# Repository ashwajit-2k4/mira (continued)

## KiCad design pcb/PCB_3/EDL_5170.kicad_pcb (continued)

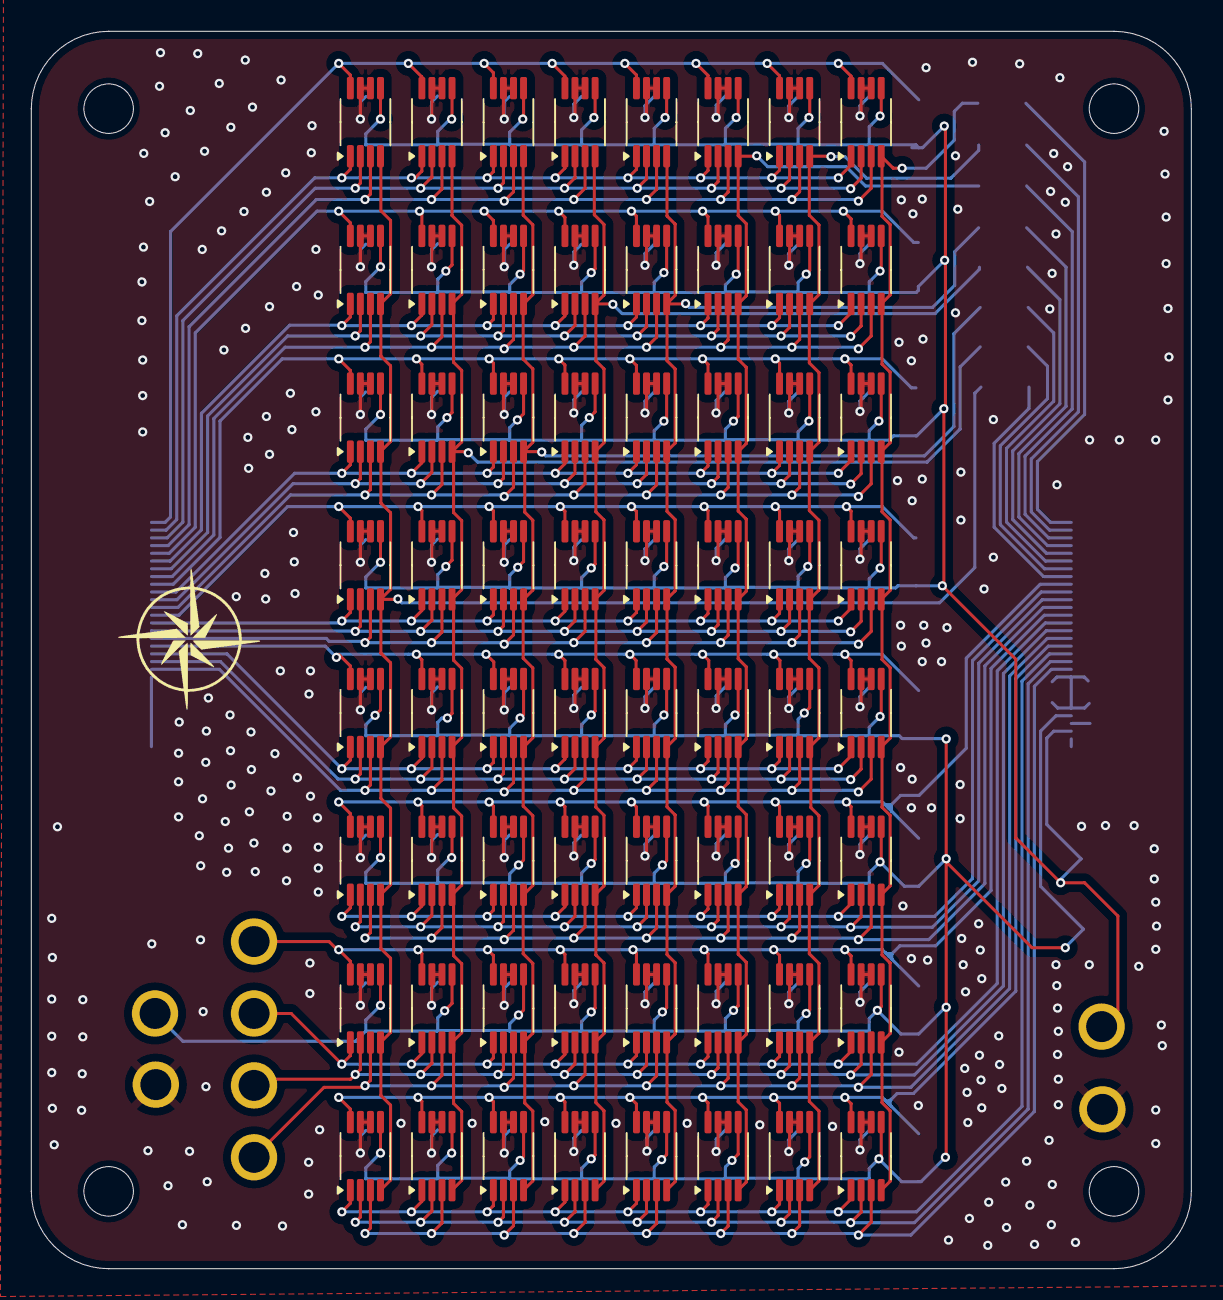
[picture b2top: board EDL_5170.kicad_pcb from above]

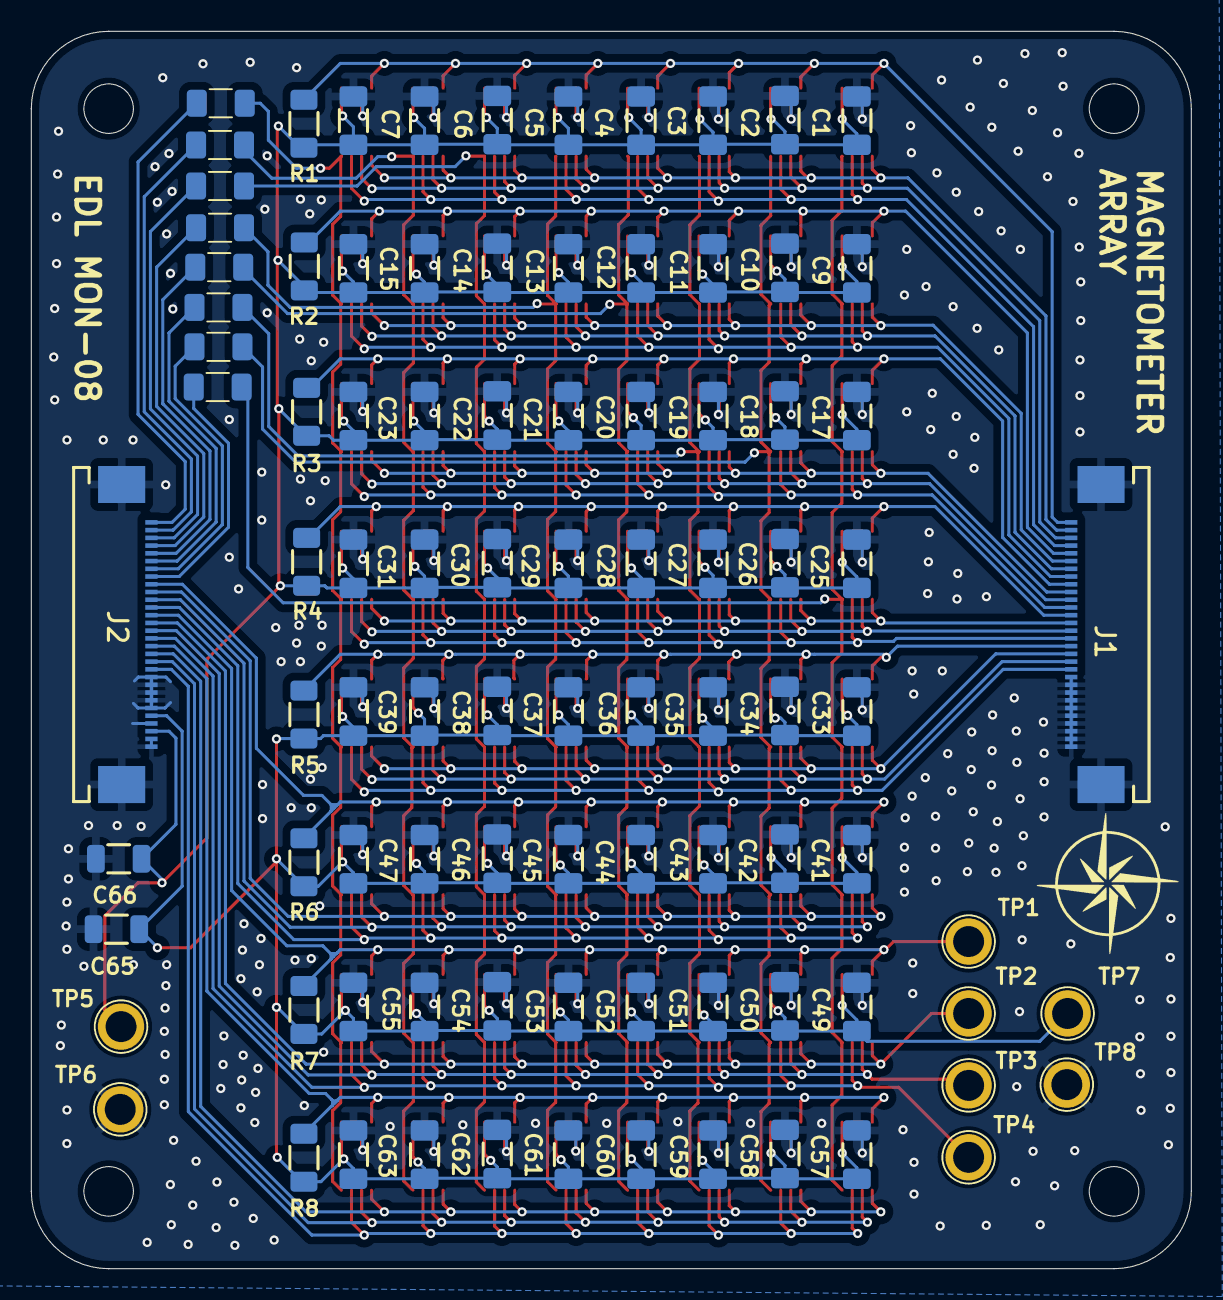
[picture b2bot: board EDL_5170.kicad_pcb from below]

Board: 2 copper layers, 75.0 x 80.0 mm, 156 parts (92 on the bottom side), 51 nets.

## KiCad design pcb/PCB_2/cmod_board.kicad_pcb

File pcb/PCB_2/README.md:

# CMOD Interface PCB

This PCB is designed to work in conjunction with the **TMAG3001 Sensor Array PCB**, forming a complete sensor head system. It serves as the interface between the microcontroller and the sensor array.

## Overview

- **Purpose**: Interface the TMAG3001 sensor array with a CMOD FPGA module  
- **CMOD Support**: Two sets of pin headers to securely mount the CMOD  
- **Signal Routing**: All signals are routed via ribbon cable connectors coming from the TMAG3001 Sensor Array PCB  
- **Power Supply**:  
  - Screw terminal block for providing power to both the FPGA and the sensor array  
  - Switches included to control the power supply to different sections

---

## Features

- **Ribbon Cable Connectors**:  
  - Located on both edges of the PCB  
  - Carry all signal lines from the sensor array PCB  

- **Power Interface**:  
  - Screw terminal for 3.3V/5V input  
  - Power control switches to selectively enable/disable supply to the FPGA and sensor PCB  

- **Mechanical Support**:  
  - Dual header slots to mount a CMOD A7 or similar FPGA board securely

---

## Files & Resources

The repository folders include:
- **Schematic**
- **PCB Layout**
- **3D Renders**
- **Assembled PCB Images**

---

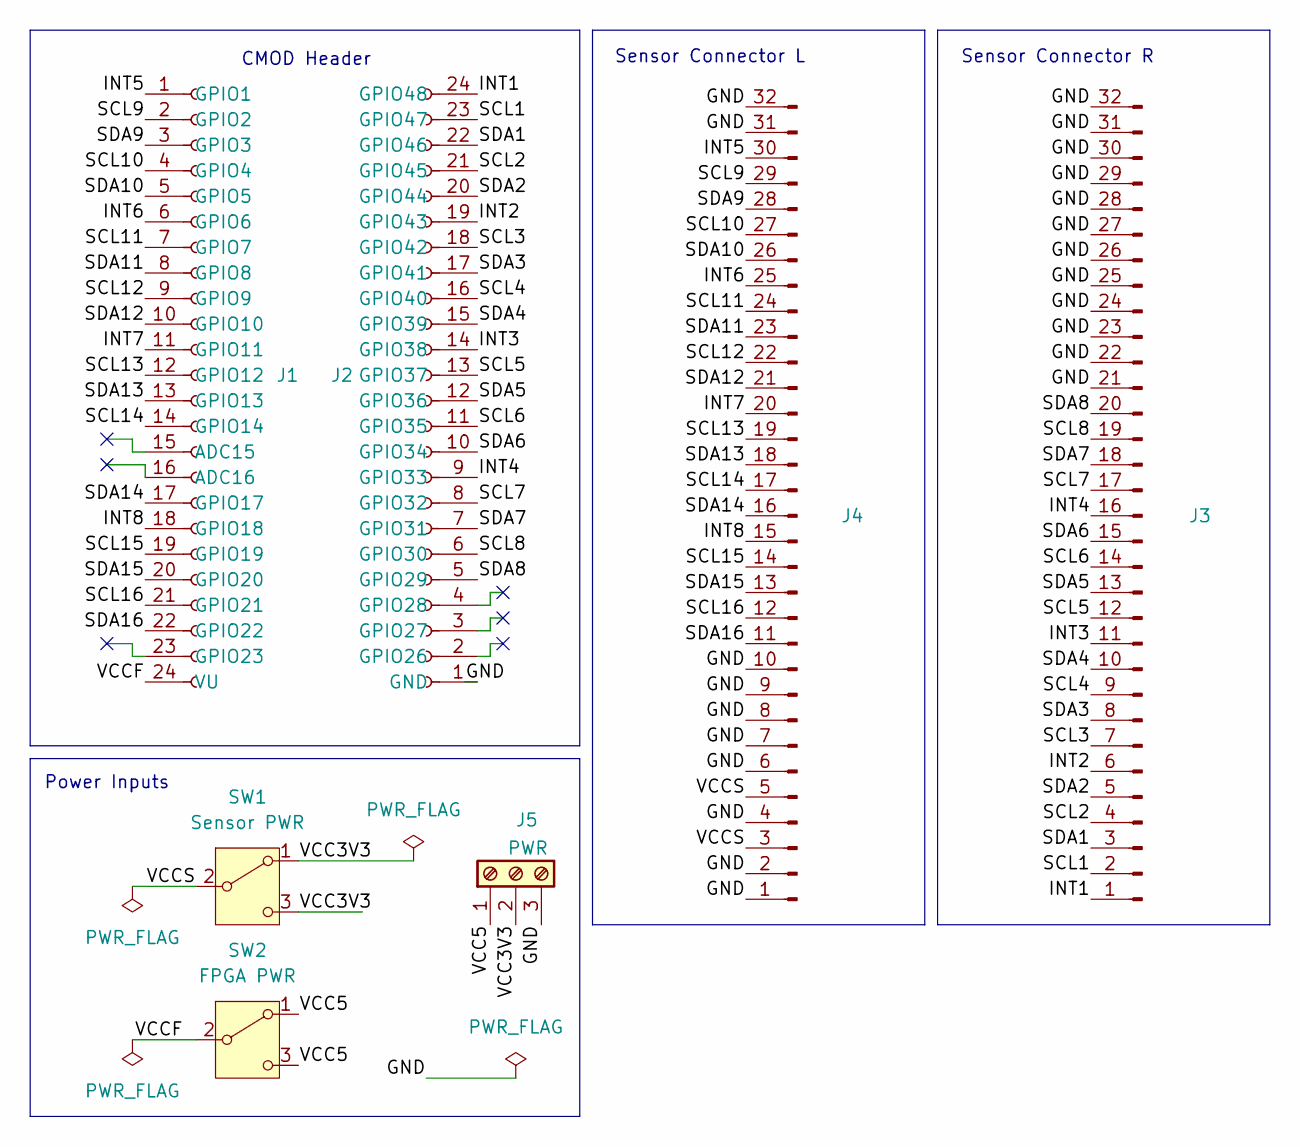
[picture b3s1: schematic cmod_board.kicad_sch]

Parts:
J1: PinSocket_1x24_P2.54mm_Vertical
J2: Conn_01x24_Socket; PinSocket_1x24_P2.54mm_Vertical
J3, J4: Conn_01x32_Pin; 52435-3071
J5: PWR; TerminalBlock_Phoenix_PT-1,5-3-3.5-H_1x03_P3.50mm_Horizontal
SW1: Sensor PWR; SPDT Switch 3 mm
SW2: FPGA PWR; SPDT Switch 3 mm

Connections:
/GND: J2.1 (GND), J3.21, J3.22, J3.23, J3.24, J3.25, J3.26, J3.27, J3.28, J3.29, J3.30, J3.31, J3.32, J4.1, J4.2, J4.4, J4.6, J4.7, J4.8, J4.9, J4.10, J4.31, J4.32, J5.3
/INT1: J2.24 (GPIO48), J3.1
/INT2: J2.19 (GPIO43), J3.6
/INT3: J2.14 (GPIO38), J3.11
/INT4: J2.9 (GPIO33), J3.16
/INT5: J1.1 (GPIO1), J4.30
/INT6: J1.6 (GPIO6), J4.25
/INT7: J1.11 (GPIO11), J4.20
/INT8: J1.18 (GPIO18), J4.15
/SCL1: J2.23 (GPIO47), J3.2
/SCL2: J2.21 (GPIO45), J3.4
/SCL3: J2.18 (GPIO42), J3.7
/SCL4: J2.16 (GPIO40), J3.9
/SCL5: J2.13 (GPIO37), J3.12
/SCL6: J2.11 (GPIO35), J3.14
/SCL7: J2.8 (GPIO32), J3.17
/SCL8: J2.6 (GPIO30), J3.19
/SCL9: J1.2 (GPIO2), J4.29
/SCL10: J1.4 (GPIO4), J4.27
/SCL11: J1.7 (GPIO7), J4.24
/SCL12: J1.9 (GPIO9), J4.22
/SCL13: J1.12 (GPIO12), J4.19
/SCL14: J1.14 (GPIO14), J4.17
/SCL15: J1.19 (GPIO19), J4.14
/SCL16: J1.21 (GPIO21), J4.12
/SDA1: J2.22 (GPIO46), J3.3
/SDA2: J2.20 (GPIO44), J3.5
/SDA3: J2.17 (GPIO41), J3.8
/SDA4: J2.15 (GPIO39), J3.10
/SDA5: J2.12 (GPIO36), J3.13
/SDA6: J2.10 (GPIO34), J3.15
/SDA7: J2.7 (GPIO31), J3.18
/SDA8: J2.5 (GPIO29), J3.20
/SDA9: J1.3 (GPIO3), J4.28
/SDA10: J1.5 (GPIO5), J4.26
/SDA11: J1.8 (GPIO8), J4.23
/SDA12: J1.10 (GPIO10), J4.21
/SDA13: J1.13 (GPIO13), J4.18
/SDA14: J1.17 (GPIO17), J4.16
/SDA15: J1.20 (GPIO20), J4.13
/SDA16: J1.22 (GPIO22), J4.11
/VCC3V3: J5.2, SW1.1 (A), SW1.3 (C)
/VCC5: J5.1, SW2.1 (A), SW2.3 (C)
/VCCF: J1.24 (VU), SW2.2 (B)
/VCCS: J4.3, J4.5, SW1.2 (B)

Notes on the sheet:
CMOD Header
Sensor Connector R
Sensor Connector L
Power Inputs

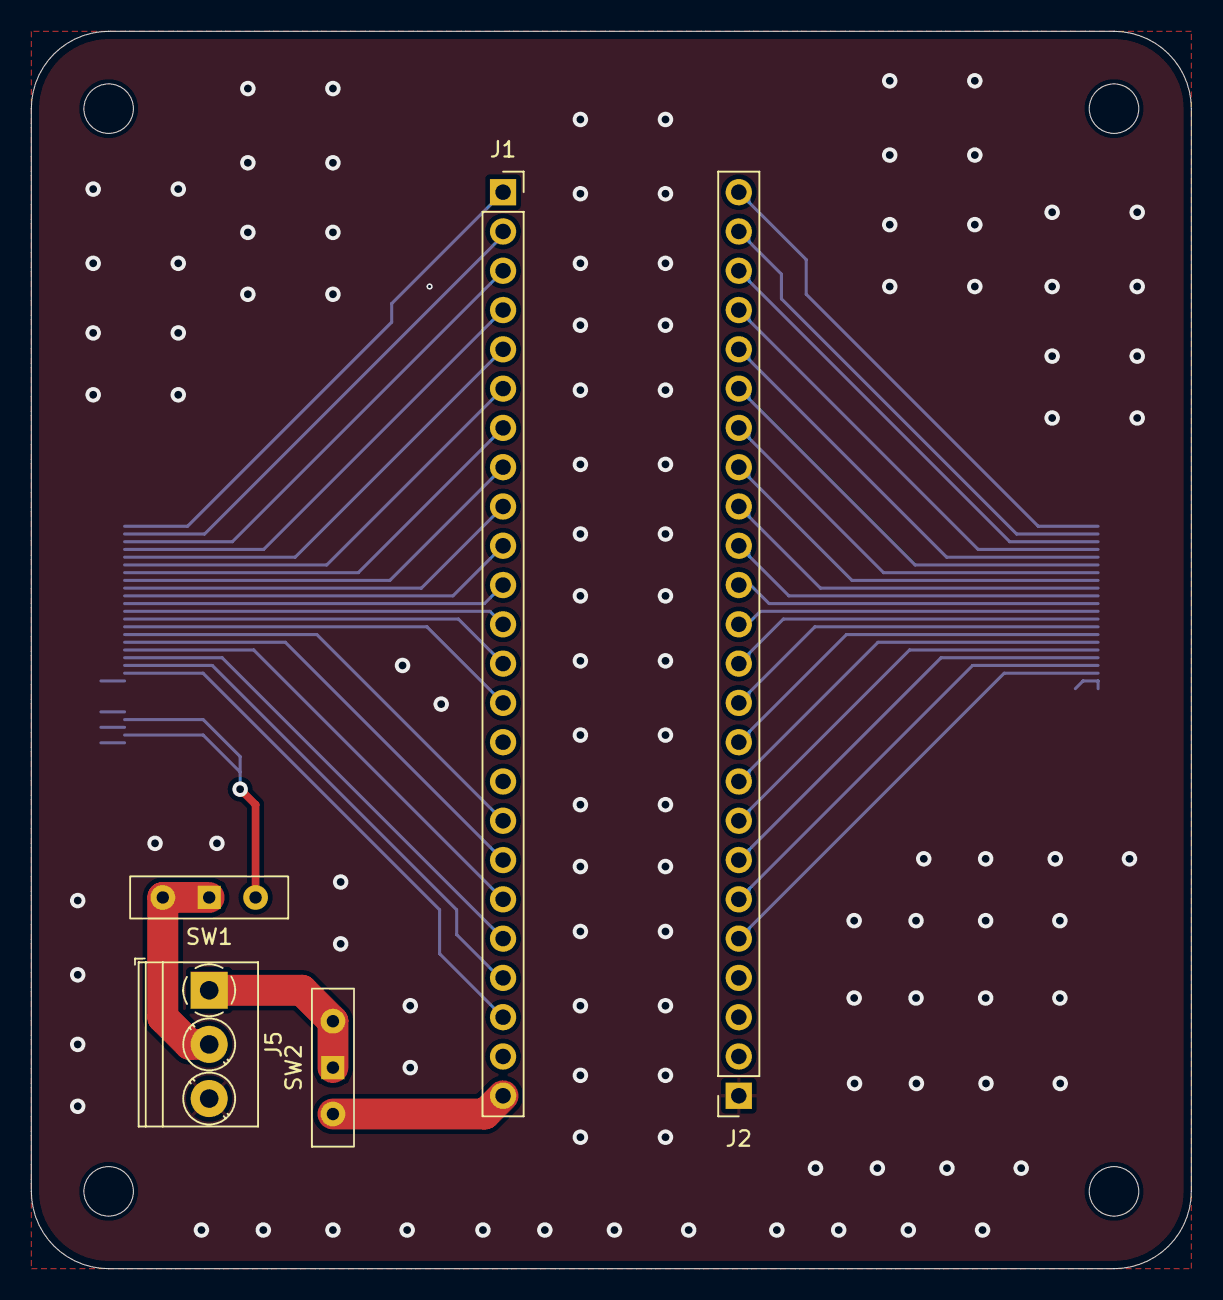
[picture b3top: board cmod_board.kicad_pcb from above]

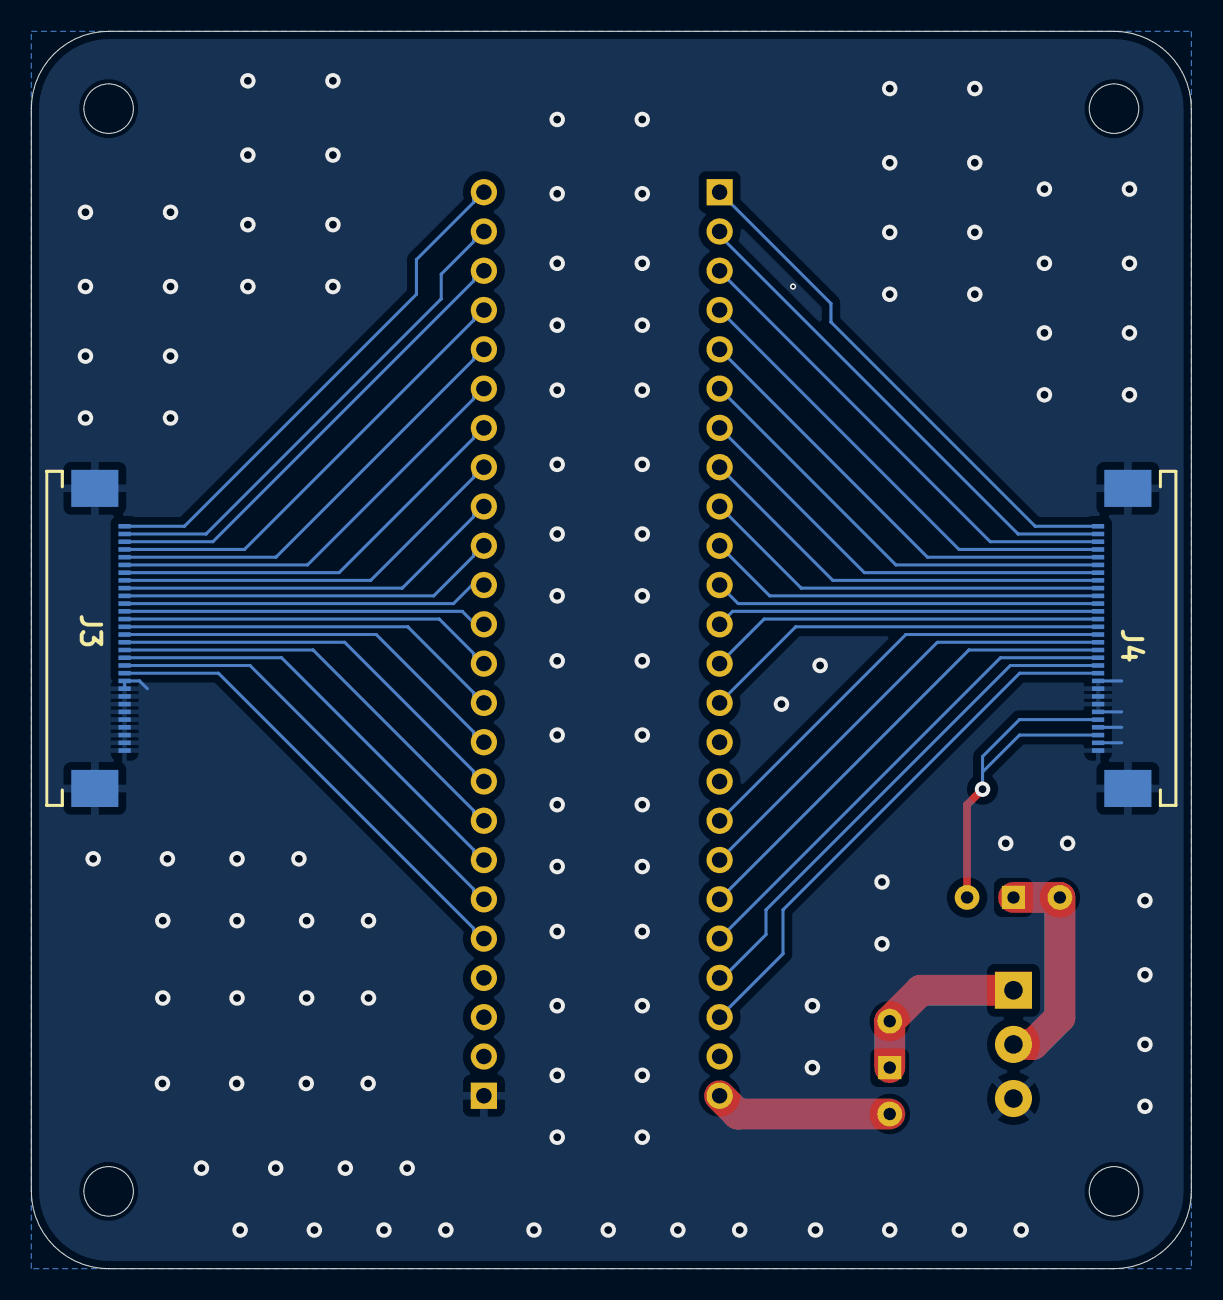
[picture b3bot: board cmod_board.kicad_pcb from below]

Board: 2 copper layers, 75.0 x 80.0 mm, 7 parts (2 on the bottom side), 45 nets.
